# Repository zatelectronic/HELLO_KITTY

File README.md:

# HELLO KITTY — placa de arte com 6 LEDs

Placa de arte Hello Kitty desenhada na serigrafia, com **6 LEDs coloridos** de 5 mm (vermelho, azul e amarelo) ligados a uma **barra de 7 pinos 90°** na borda da placa.

## Funcionalidades

- ✅ **Barra de pinos 1×07 90°** (J1) na borda — 1 GND + 6 canais
- ✅ **6 LEDs 5 mm** THT (D1–D6): D1 vermelho, D2 azul, D3 amarelo, D4 vermelho, D5 vermelho, D6 amarelo
- ✅ **6 resistores 220 Ω 1/4 W** axiais (R1–R6), um por LED
- ✅ Liga em qualquer microcontrolador (Arduino, ESP32, Pico) com GND comum
- ✅ **Arte na serigrafia** recortada em volta de cada LED (nada de tinta sobre pad)
- ✅ Placa **100 × 100 mm**, 2 camadas, plano de GND nas duas faces

## Ligação dos LEDs

| LED | Cor | Resistor | Pino J1 / sinal | Corrente @ 5 V |
|---|---|---|---|---|
| D1 | vermelho | R1 220 Ω | J1.2 · LED1 | ≈ 13,6 mA |
| D2 | azul | R2 220 Ω | J1.3 · LED2 | ≈ 9,1 mA |
| D3 | amarelo | R3 220 Ω | J1.4 · LED3 | ≈ 13,6 mA |
| D4 | vermelho | R4 220 Ω | J1.5 · LED4 | ≈ 13,6 mA |
| D5 | vermelho | R5 220 Ω | J1.6 · LED5 | ≈ 13,6 mA |
| D6 | amarelo | R6 220 Ω | J1.7 · LED6 | ≈ 13,6 mA |

Cada canal: **pino → 220 Ω → LED → GND** (nível alto acende). Todos acesos ≈ **77 mA**.

| J1 | Sinal |
|---|---|
| 1 | GND |
| 2 | LED1 (D1) |
| 3 | LED2 (D2) |
| 4 | LED3 (D3) |
| 5 | LED4 (D4) |
| 6 | LED5 (D5) |
| 7 | LED6 (D6) |

> Em 3,3 V (ESP32 / Pico) os LEDs vermelho/amarelo ficam com ≈ 6 mA e o azul fica bem fraco (≈ 1 mA).

## Diagrama de blocos

```
┌──────────────────────┐   LED1 … LED6      ┌──────────────────────────┐
│  J1 barra 1×07 90°   │ ─────────────────► │ 6 × [220 Ω → LED 5 mm]   │
│  1 GND · 2–7 canais  │ ◄──────── GND ──── │  R1–R6       D1–D6       │
└──────────────────────┘                    └──────────────────────────┘
```

## Firmware

`firmware/HELLO_KITTY/HELLO_KITTY.ino` — exemplo simples (corrida, pisca alternado e aleatório). Ligação: **Arduino D8 … D13 → J1 pinos 2 … 7**, GND → J1 pino 1.

## Esquemático (KiCad 10)

| Pág. | Folha | Conteúdo |
|---|---|---|
| 1 | Capa (A2) | blocos, mapa dos LEDs na placa, vista 3D |
| 2 | LEDS | D1–D6 + R1–R6 |
| 3 | CONN | J1 (barra 1×07 90°) + PWR_FLAG do GND |

## Lista de materiais

| Ref. | Qtd | Valor | Footprint |
|---|---|---|---|
| D1,D4,D5 | 3 | LED 5 mm vermelho | ZAT_LED:LED_D5.0mm_Red |
| D2 | 1 | LED 5 mm azul | ZAT_LED:LED_D5.0mm_Blue |
| D3,D6 | 2 | LED 5 mm amarelo | ZAT_LED:LED_D5.0mm_Yellow |
| J1 | 1 | Barra de pinos 1×07 90° | ZAT_Connector:PinHeader_1x07_P2.54mm_RightAngle_EdgeMount |
| R1–R6 | 6 | 220 Ω 1/4 W | ZAT_Resistor_THT:R_Axial_DIN0204_L3.6mm_D1.6mm_P7.62mm_Horizontal_220R |

## Arquivos

- `HELLO_KITTY.kicad_pro` — projeto KiCad 10 (bibliotecas globais KiCad + ZAT, sem pasta lib)
- `Zat_TitleBlock.kicad_wks` — moldura Zat Electronic
- `packages3D/` — modelos 3D usados na vista 3D

## Licença / autor

Projeto **Zat Electronic** — Kenneth Zat · Osasco/SP · hardware aberto.

*Revisão R01 — 2026-11-12 — KiCad 10.*

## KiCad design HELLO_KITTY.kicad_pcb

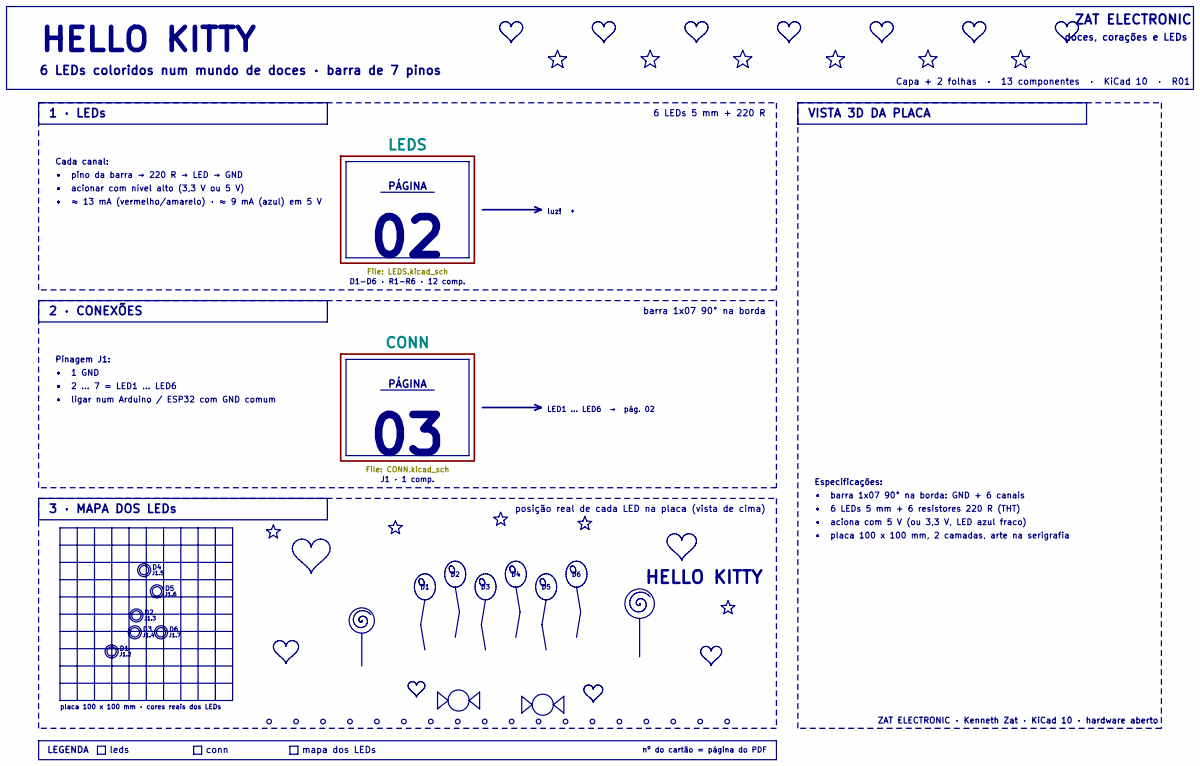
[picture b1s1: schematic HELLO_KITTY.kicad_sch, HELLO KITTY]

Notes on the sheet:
Pinagem J1:
6 LEDs 5 mm + 220 R
D1-D6 · R1-R6 · 12 comp.
HELLO KITTY
placa 100 x 100 mm · cores reais dos LEDs
PÁGINA
Capa + 2 folhas · 13 componentes · KiCad 10 · R01
• aciona com 5 V (ou 3,3 V, LED azul fraco)
• ligar num Arduino / ESP32 com GND comum
J1.7
conn
1 · LEDs
• placa 100 x 100 mm, 2 camadas, arte na serigrafia
barra 1x07 90° na borda
ZAT ELECTRONIC · Kenneth Zat · KiCad 10 · hardware aberto
Especificações:
2 · CONEXÕES
• pino da barra → 220 R → LED → GND
Cada canal:
• 1 GND
• 6 LEDs 5 mm + 6 resistores 220 R (THT)
leds
• 2 … 7 = LED1 … LED6
• acionar com nível alto (3,3 V ou 5 V)
VISTA 3D DA PLACA
J1.5
LEGENDA
mapa dos LEDs
luz! ✦
J1.3
doces, corações e LEDs
J1 · 1 comp.
• ≈ 13 mA (vermelho/amarelo) · ≈ 9 mA (azul) em 5 V
LED1 … LED6 → pág. 02
ZAT ELECTRONIC
J1.6
J1.2
nº do cartão = página do PDF
6 LEDs coloridos num mundo de doces · barra de 7 pinos
posição real de cada LED na placa (vista de cima)

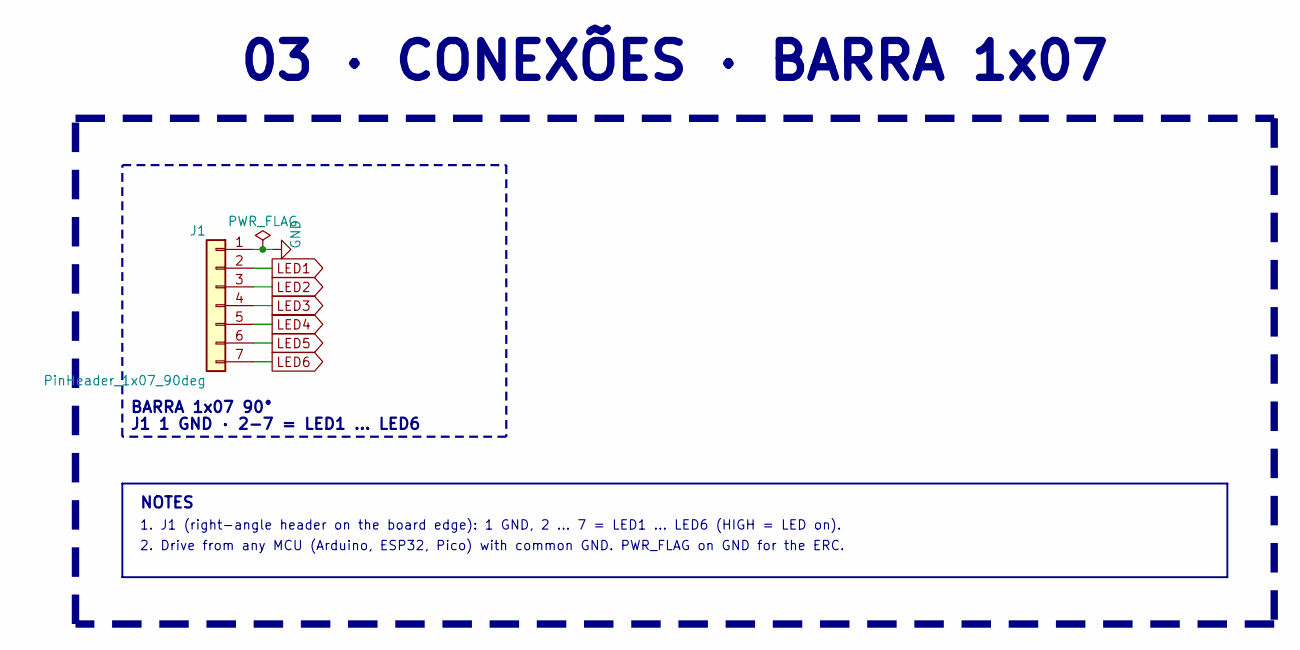
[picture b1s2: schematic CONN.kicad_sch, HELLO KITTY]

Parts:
J1: PinHeader_1x07_90deg; PinHeader_1x07_P2.54mm_RightAngle_EdgeMount

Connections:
GND: J1.1; also elsewhere on the board
LED1: J1.2; also elsewhere on the board
LED2: J1.3; also elsewhere on the board
LED3: J1.4; also elsewhere on the board
LED4: J1.5; also elsewhere on the board
LED5: J1.6; also elsewhere on the board
LED6: J1.7; also elsewhere on the board

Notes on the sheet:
BARRA 1x07 90°
J1 1 GND · 2-7 = LED1 ... LED6
1. J1 (right-angle header on the board edge): 1 GND, 2 ... 7 = LED1 ... LED6 (HIGH = LED on).
NOTES
2. Drive from any MCU (Arduino, ESP32, Pico) with common GND. PWR_FLAG on GND for the ERC.
03 · CONEXÕES · BARRA 1x07

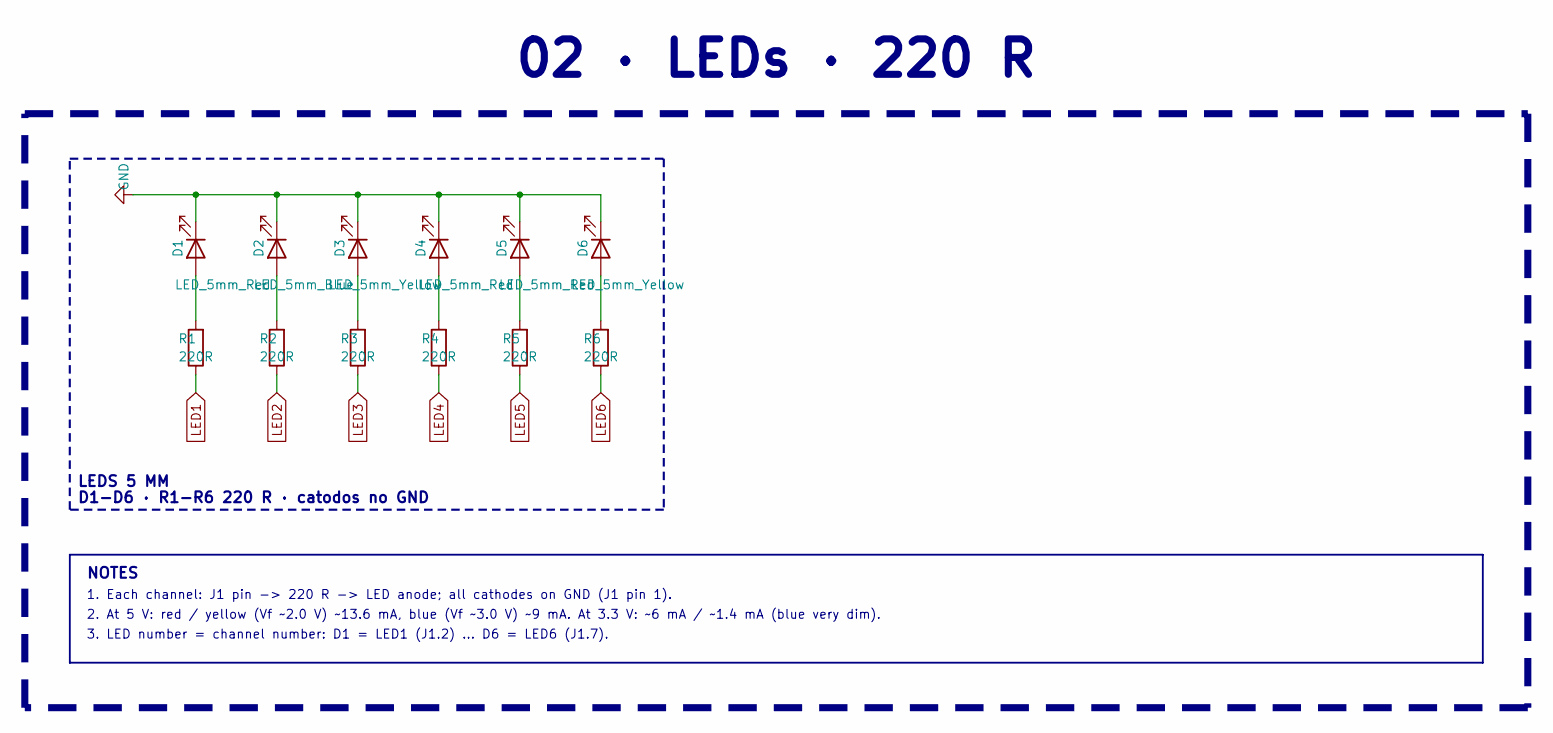
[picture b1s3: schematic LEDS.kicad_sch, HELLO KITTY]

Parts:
D1, D4, D5: LED_5mm_Red; LED_D5.0mm_Red
D2: LED_5mm_Blue; LED_D5.0mm_Blue
D3, D6: LED_5mm_Yellow; LED_D5.0mm_Yellow
R1, R2, R3, R4, R5, R6: 220R; R_Axial_DIN0204_L3.6mm_D1.6mm_P7.62mm_Horizontal_220R

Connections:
GND: D1.1 (K), D2.1 (K), D3.1 (K), D4.1 (K), D5.1 (K), D6.1 (K); also elsewhere on the board
LED1: R1.1; also elsewhere on the board
LED2: R2.1; also elsewhere on the board
LED3: R3.1; also elsewhere on the board
LED4: R4.1; also elsewhere on the board
LED5: R5.1; also elsewhere on the board
LED6: R6.1; also elsewhere on the board
unnamed: D1.2 (A), R1.2
unnamed: D2.2 (A), R2.2
unnamed: D3.2 (A), R3.2
unnamed: D4.2 (A), R4.2
unnamed: D5.2 (A), R5.2
unnamed: D6.2 (A), R6.2

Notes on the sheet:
3. LED number = channel number: D1 = LED1 (J1.2) ... D6 = LED6 (J1.7).
1. Each channel: J1 pin -> 220 R -> LED anode; all cathodes on GND (J1 pin 1).
D1-D6 · R1-R6 220 R · catodos no GND
LEDS 5 MM
NOTES
02 · LEDs · 220 R
2. At 5 V: red / yellow (Vf ~2.0 V) ~13.6 mA, blue (Vf ~3.0 V) ~9 mA. At 3.3 V: ~6 mA / ~1.4 mA (blue very dim).

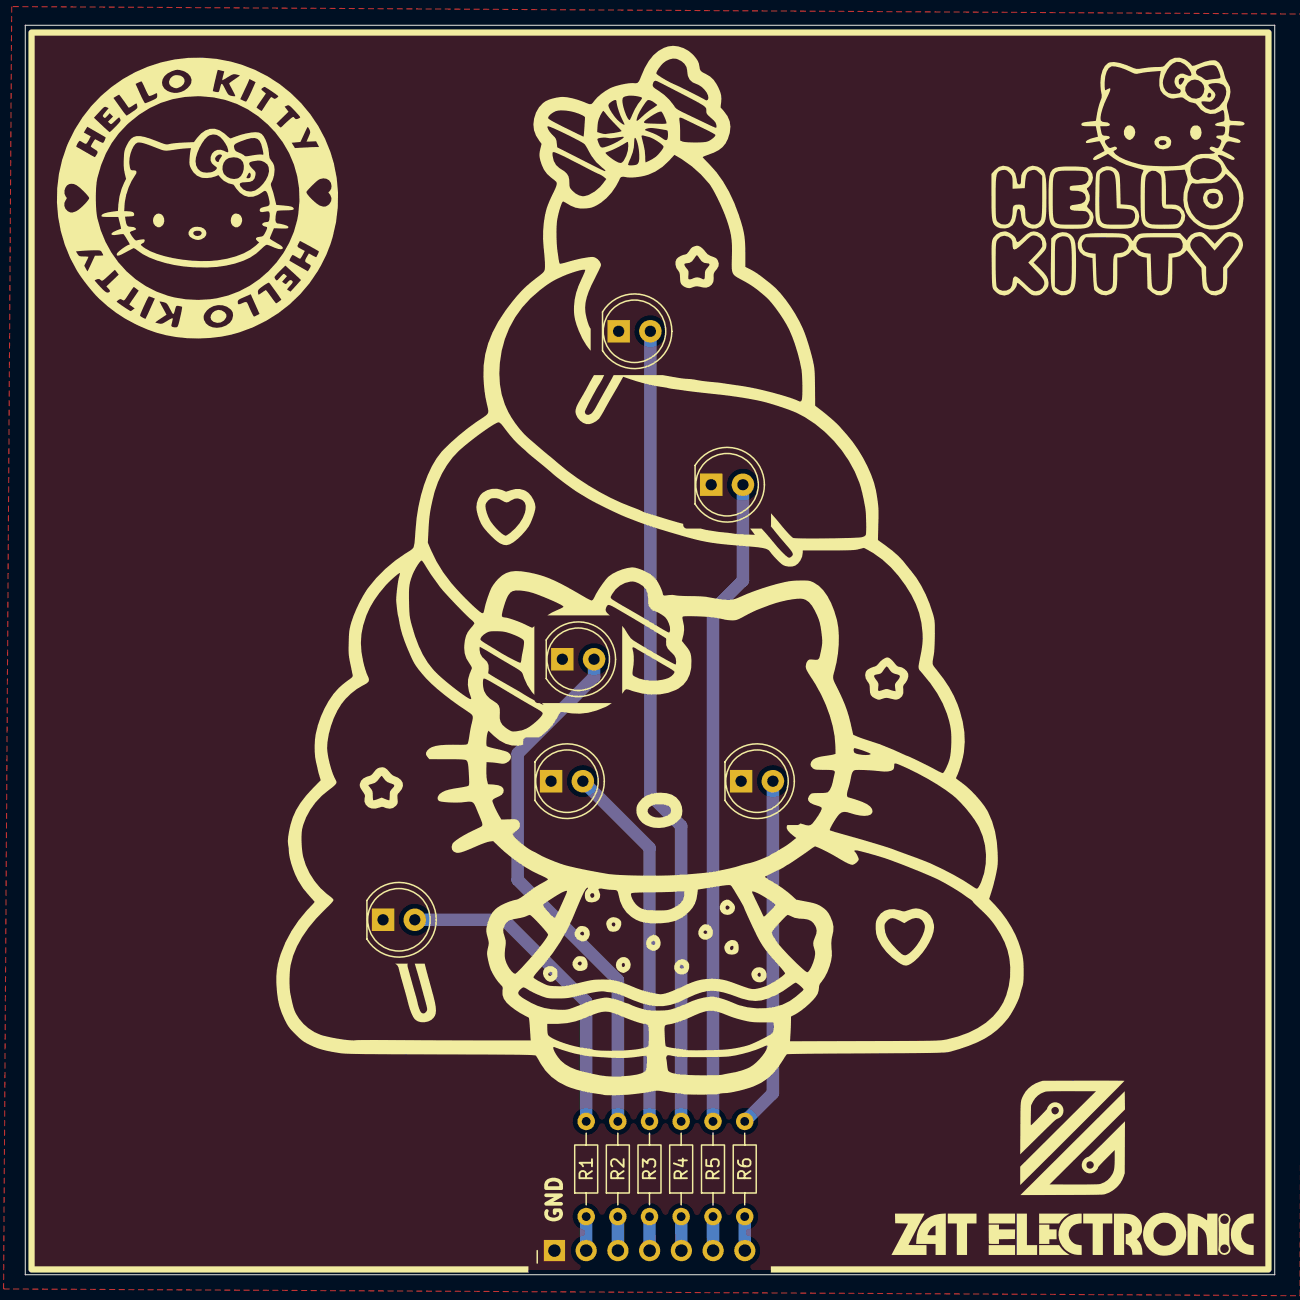
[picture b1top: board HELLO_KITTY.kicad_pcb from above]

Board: 2 copper layers, 100.0 x 100.0 mm, 13 parts (0 on the bottom side), 13 nets.

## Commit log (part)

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2026-06-28 commit_3
